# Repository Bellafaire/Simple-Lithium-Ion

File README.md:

# Simple Lithium Ion
A simple to use lithium ion boost, charge, and protection board designed to directly solder to standard 2.54mm perfboard for easier projects. For project logs and more in-depth information about the project please check out the project's hackaday.io page here: 
https://hackaday.io/project/167078-simple-lithium-ion

## Features
- On-board lithium ion charging 
- Over current protection
- Over/Under voltage protection
- 5V output from single battery cell

## License
MIT

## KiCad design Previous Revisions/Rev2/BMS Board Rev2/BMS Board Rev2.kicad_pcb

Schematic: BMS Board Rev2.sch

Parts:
C1, C2, C3, C4, C5: 10uF; C_0805_2012Metric
D1: LED; LED_0805_2012Metric
D2: SK34WA; D_SOD-123F
J1, J3: Conn_01x06_Male; PinHeader_1x06_P2.54mm_Vertical
J2: USB_B_Micro; USB_Micro-B_Molex_47346-0001
L1: 4.7u (BCIHP0730-4R7M); L_7x7x3
R1: 220; R_0805_2012Metric
R2: 1k; R_0805_2012Metric
R3: 2k; R_0805_2012Metric
R4: 100; R_0805_2012Metric
R5: 220k; R_0805_2012Metric
R6: 3.3k; R_0805_2012Metric
U1: DW01; SOT-23-6
U2: SLM4055; SOT-23-5
U3, U4: NCE3420; SOT-23
U5: MT3608; SOT-23-6

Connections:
BAT+: C3.1, C4.1, J1.1, J1.2, J1.3, L1.2, R4.2, U2.1, U5.4, U5.5
BAT-: C1.2, C2.2, C3.2, J1.4, J1.5, J1.6, J2.5 (GND), J2.6 (Shield), R3.2, U1.6, U2.2, U4.2
GND_Protected: C4.2, C5.2, J3.1, J3.2, J3.3, R2.2, R6.2, U3.3, U5.2
unnamed: C1.1, D1.2 (A), J2.1 (VBUS), U2.4
unnamed: C2.1, R4.1, U1.5
unnamed: C5.1, D2.1, J3.4, J3.5, J3.6, R5.1
unnamed: D1.1 (K), R1.1
unnamed: D2.2, L1.1, U5.1
unnamed: R2.1, U1.2
unnamed: R3.1, U2.5
unnamed: R5.2, R6.1, U5.3
unnamed: U1.1, U3.1
unnamed: U1.3, U4.1
unnamed: U3.2, U4.3
chrg_indicator: R1.2, U2.3

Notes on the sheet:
This resistor configuration yields a 4.6v output, please revise

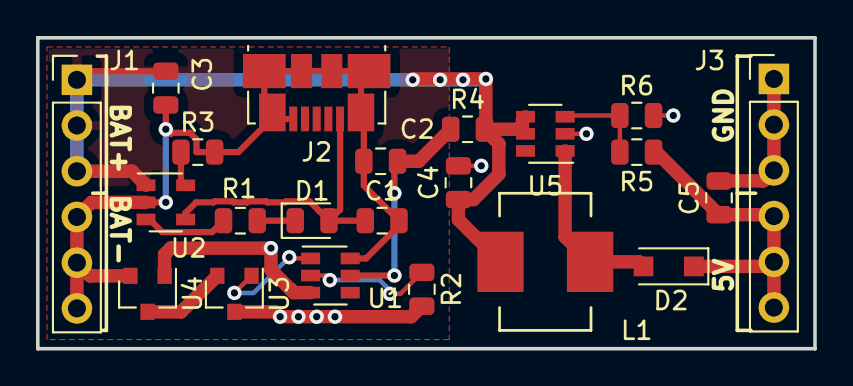
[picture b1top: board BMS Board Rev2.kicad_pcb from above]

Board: 2 copper layers, 43.2 x 17.3 mm, 22 parts (0 on the bottom side), 15 nets.

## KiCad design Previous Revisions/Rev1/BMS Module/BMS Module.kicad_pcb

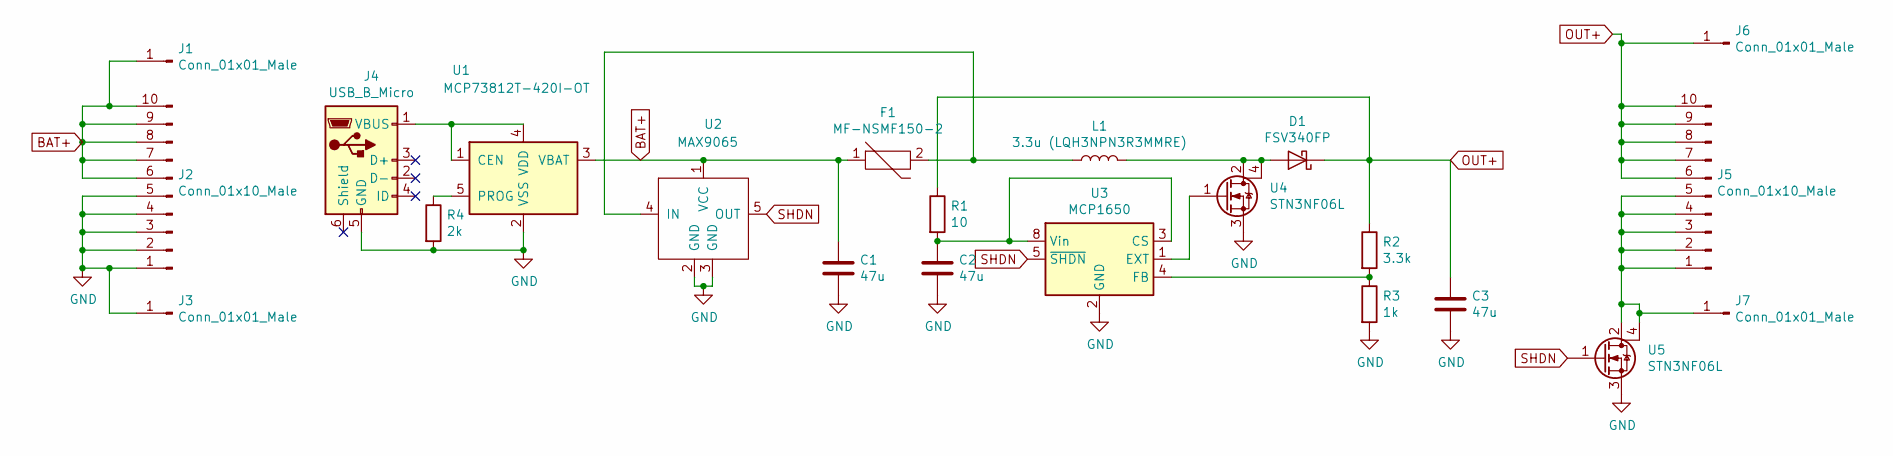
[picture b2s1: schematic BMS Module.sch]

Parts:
C1, C2, C3: 47u; C_1210_3225Metric
D1: FSV340FP; D_SOD-123
F1: MF-NSMF150-2; Fuse_1206_3216Metric
J1, J3, J6, J7: Conn_01x01_Male; PinHeader_1x01_P2.54mm_Vertical
J2, J5: Conn_01x10_Male; PinHeader_1x10_P2.54mm_Vertical
J4: USB_B_Micro; USB_Micro-B_GCT_USB3076-30-A
L1: 3.3u (LQH3NPN3R3MMRE); L_Taiyo-Yuden_MD-3030
R1: 10; R_0805_2012Metric
R2: 3.3k; R_0805_2012Metric
R3: 1k; R_0805_2012Metric
R4: 2k; R_0805_2012Metric
U1: MCP73812T-420I-OT; SOT-23-5
U2: MAX9065; SOT-23-5
U3: MCP1650; MSOP-8_3x3mm_P0.65mm
U4, U5: STN3NF06L; SOT-223

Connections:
BAT+: C1.1, F1.1, J1.1, J2.6, J2.7, J2.8, J2.9, J2.10, U1.3 (VBAT), U2.1 (VCC)
GND: C1.2, C2.2, C3.2, J2.1, J2.2, J2.3, J2.4, J2.5, J3.1, J4.5 (GND), R3.2, R4.2, U1.2 (VSS), U2.2 (GND), U2.3 (GND), U3.2 (GND), U4.3, U5.3
unnamed: C2.1, R1.2, U3.3 (CS), U3.8 (Vin)
unnamed: D1.2 (A), L1.2, U4.2, U4.4
unnamed: F1.2, L1.1, U2.4 (IN)
unnamed: J4.1 (VBUS), U1.1 (CEN), U1.4 (VDD)
unnamed: J5.1, J5.2, J5.3, J5.4, J5.5, J7.1, U5.2, U5.4
unnamed: R2.2, R3.1, U3.4 (FB)
unnamed: R4.1, U1.5 (PROG)
unnamed: U3.1 (EXT), U4.1
OUT+: C3.1, D1.1 (K), J5.6, J5.7, J5.8, J5.9, J5.10, J6.1, R1.1, R2.1
SHDN: U2.5 (OUT), U3.5 (~SHDN), U5.1

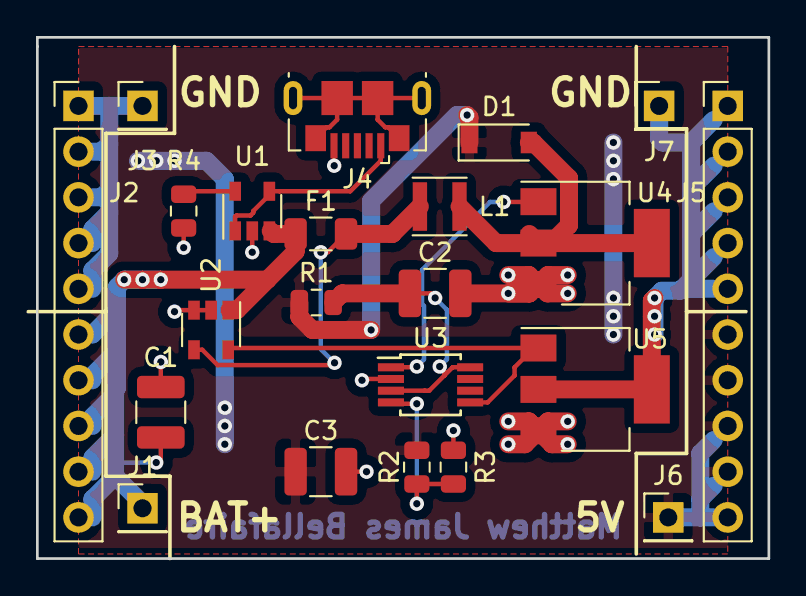
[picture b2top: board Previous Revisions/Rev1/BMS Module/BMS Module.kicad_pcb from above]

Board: 2 copper layers, 40.6 x 29.0 mm, 22 parts (0 on the bottom side), 12 nets.

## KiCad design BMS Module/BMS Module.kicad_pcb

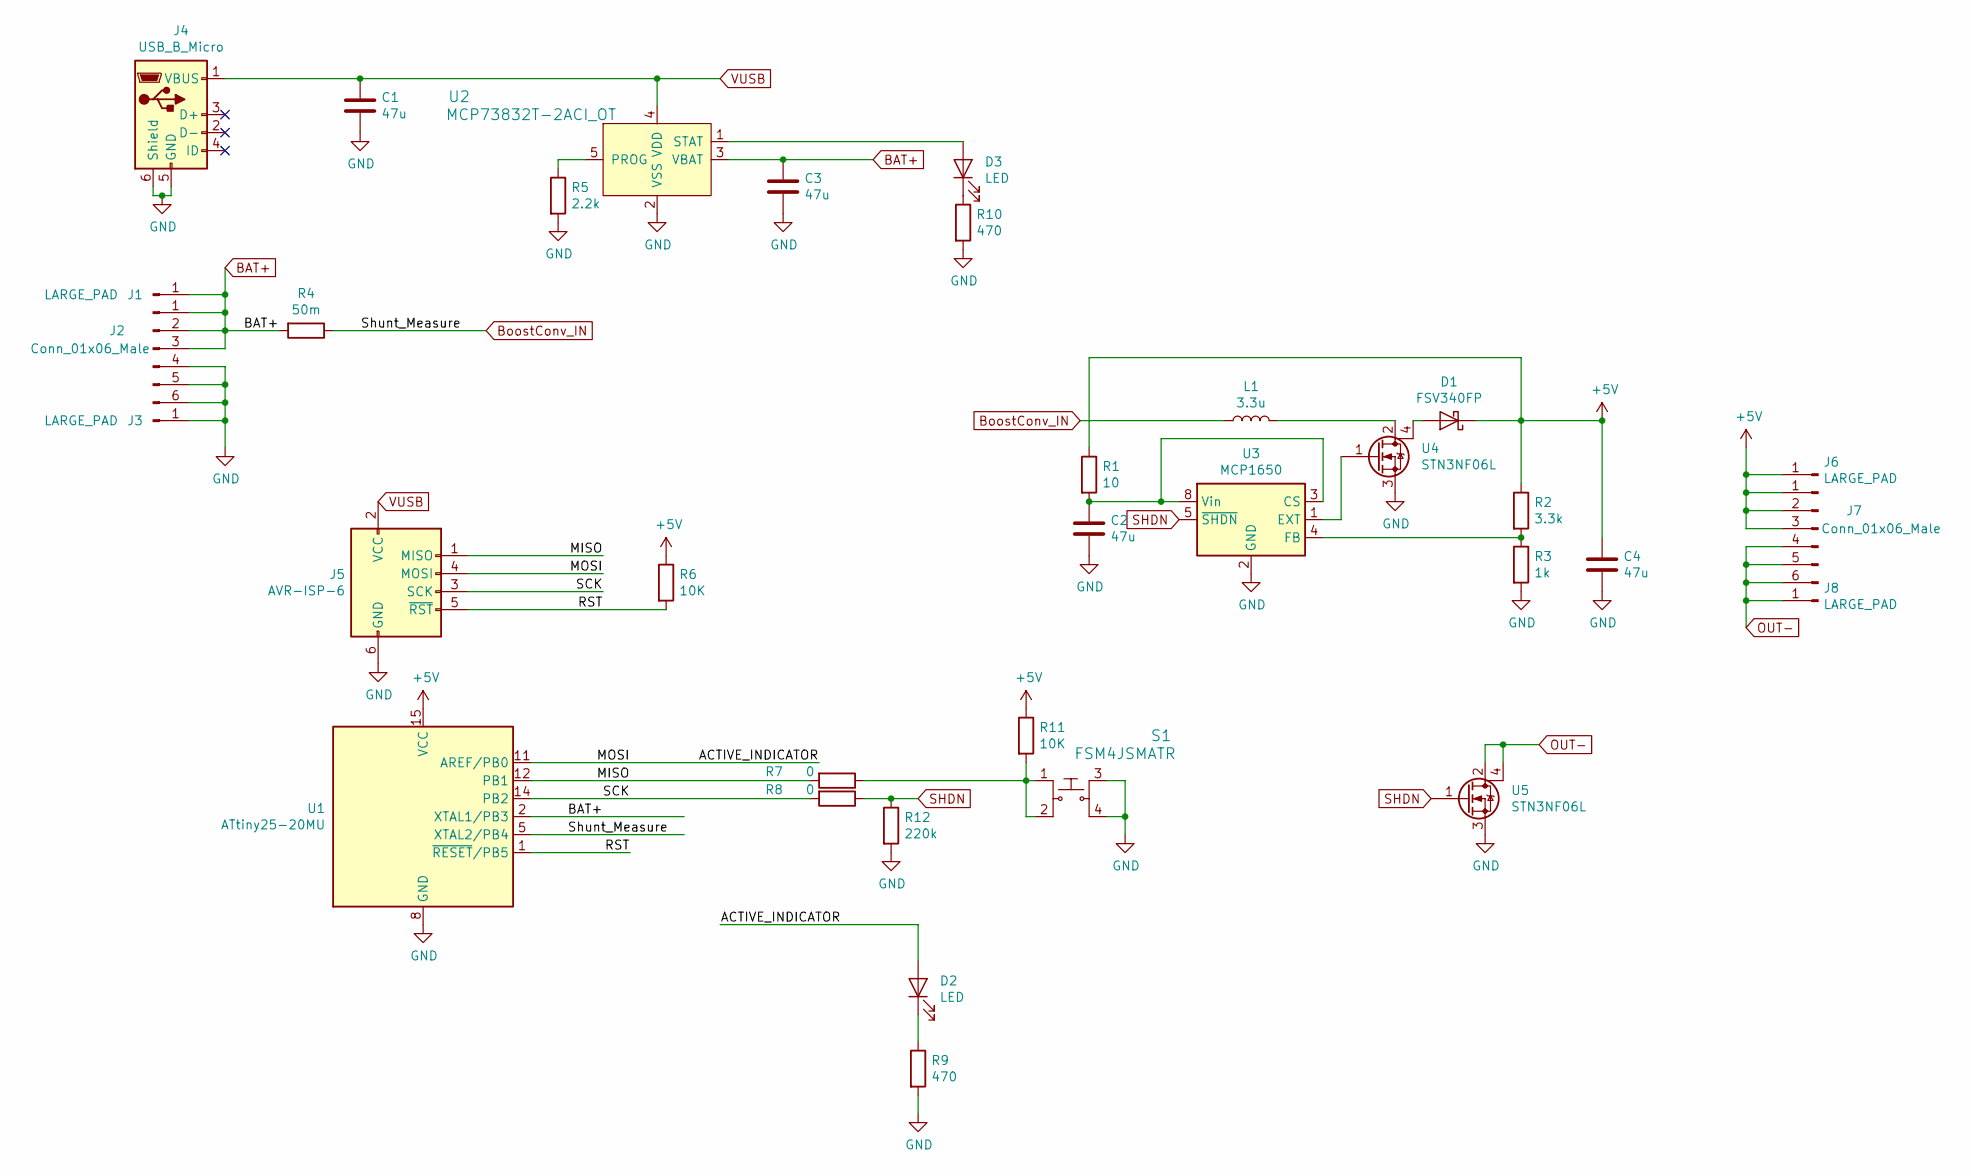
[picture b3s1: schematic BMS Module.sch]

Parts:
C1, C2, C3, C4: 47u; C_1210_3225Metric; digikey 1276-3064-1-ND
D1: FSV340FP; D_SOD-123; digikey FSV340FPCT-ND
D2, D3: LED; LED_0805_2012Metric_Castellated
J1, J3, J6, J8: LARGE_PAD
J2, J7: Conn_01x06_Male; PinHeader_1x06_P2.54mm_Vertical
J4: USB_B_Micro; USB_Micro_B_Female_10118192; digikey 609-4613-1-ND
J5: AVR-ISP-6; PinHeader_2x03_P2.54mm_Vertical
L1: 3.3u; ASPI-0630HI-3R3N-T15; digikey ASPI-0630HI-3R3M-T15CT-ND
R1: 10; R_0805_2012Metric
R2: 3.3k; R_0805_2012Metric
R3: 1k; R_0805_2012Metric
R4: 50m; R_2512_6332Metric; digikey YAG2156CT-ND
R5: 2.2k; R_0805_2012Metric
R6, R11: 10K; R_0805_2012Metric
R7, R8: 0; R_0805_2012Metric; digikey RMCF0805ZT0R00CT-ND
R9, R10: 470; R_0805_2012Metric; digikey A129745CT-ND
R12: 220k; R_0805_2012Metric
S1: FSM4JSMATR; Switch_Tactile_SMD_6x6mm; MPN FSM4JSMATR; digikey 450-1759-1-ND
U1: ATtiny25-20MU; QFN-20-1EP_4x4mm_P0.5mm_EP2.25x2.25mm; digikey 1611-ATTINY25V-15MTCT-ND
U2: MCP73832T-2ACI_OT; SOT-753; MPN MCP73832T-2ACI/OT; digikey MCP73832T-2ACI/OTCT-ND
U3: MCP1650; MSOP-8_3x3mm_P0.65mm; digikey MCP1650S-E/MS-ND
U4, U5: STN3NF06L; SOT-223; digikey 497-3177-1-ND

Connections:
+5V: C4.1, D1.1 (K), J6.1, J7.1, J7.2, J7.3, R1.1, R2.1, R6.1, R11.1, U1.15 (VCC)
/ACTIVE_INDICATOR: D2.2 (A), J5.4 (MOSI), U1.11 (AREF/PB0)
/MISO: J5.1 (MISO), R7.2, U1.12 (PB1)
/RST: J5.5 (~RST), R6.2, U1.1 (~RESET~/PB5)
/SCK: J5.3 (SCK), R8.2, U1.14 (PB2)
BAT+: C3.1, J1.1, J2.1, J2.2, J2.3, R4.2, U1.2 (XTAL1/PB3), U2.3 (VBAT)
BoostConv_IN: L1.1, R4.1, U1.5 (XTAL2/PB4)
GND: C1.2, C2.2, C3.2, C4.2, J2.4, J2.5, J2.6, J3.1, J4.5 (GND), J4.6 (Shield), J5.6 (GND), R3.2, R5.2, R9.2, R10.2, R12.2, S1.3, S1.4, U1.8 (GND), U1.21 (GND), U2.2 (VSS), U3.2 (GND), U4.3, U5.3
unnamed: C2.1, R1.2, U3.3 (CS), U3.8 (Vin)
unnamed: D1.2 (A), U4.4
unnamed: D2.1 (K), R9.1
unnamed: D3.1 (K), R10.1
unnamed: D3.2 (A), U2.1 (STAT)
unnamed: L1.2, U4.2
unnamed: R2.2, R3.1, U3.4 (FB)
unnamed: R5.1, U2.5 (PROG)
unnamed: R7.1, R11.2, S1.1, S1.2
unnamed: U3.1 (EXT), U4.1
OUT-: J7.4, J7.5, J7.6, J8.1, U5.2, U5.4
SHDN: R8.1, R12.1, U3.5 (~SHDN), U5.1
VUSB: C1.1, J4.1 (VBUS), J5.2 (VCC), U2.4 (VDD)

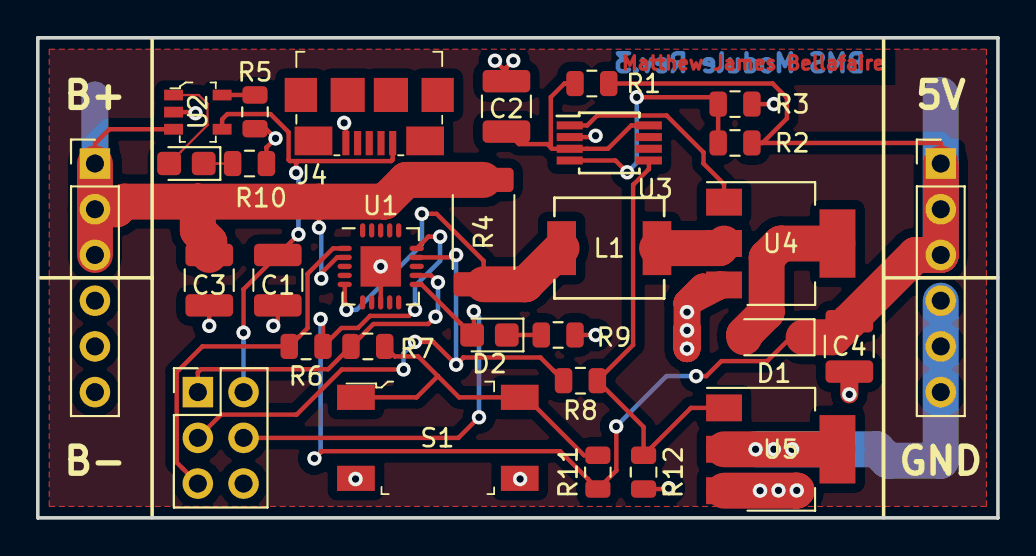
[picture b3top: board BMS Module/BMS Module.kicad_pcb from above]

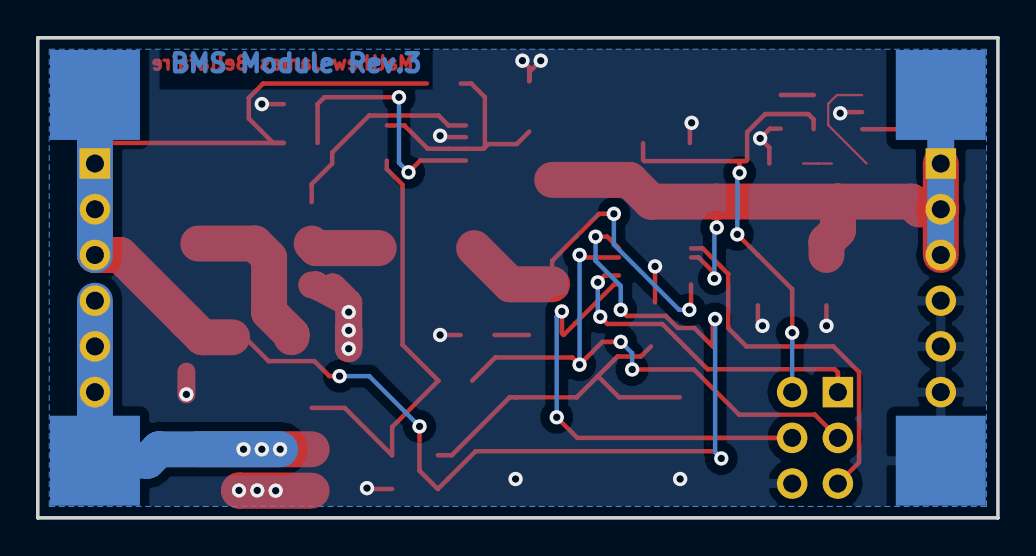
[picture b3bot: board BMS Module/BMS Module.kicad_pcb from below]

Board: 2 copper layers, 53.3 x 26.7 mm, 34 parts (4 on the bottom side), 21 nets.

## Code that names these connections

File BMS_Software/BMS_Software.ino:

#include <BatteryMonitor.h>
#define F_CPU 8000000
#include <util/delay.h> //using the arduino delay takes more flash than the util/delay.h hence why we use it instead. Actually saved about 100 bytes by doing this
#include <avr/sleep.h>
#include <avr/interrupt.h>

//be sure to enable Brown out detection at 2.7V
//core clock should be 1MHz to reduce power consumption.

#define ACTIVE_IND PB0
#define BUTTON PB1
#define SHDN PB2
#define BAT_POS 3          //ADC3
#define CURRENT_MEASURE 2  //ADC4

#define OVER_CURRENT_LIMIT 1.0
#define UNDER_VOLTAGE_THRESHOLD 3.0
#define ABSOLUTE_MINIMUM_VOLTAGE 2.7

#define BUTTON_HOLD_TO_SLEEP_MS 500
#define LOOP_DELAY 10

#define SLEEP_BUTTON_COUNT BUTTON_HOLD_TO_SLEEP_MS / LOOP_DELAY

int buttonHeldCounter = 0;

BatteryMonitor bat = BatteryMonitor(BAT_POS, CURRENT_MEASURE);

//disable sleep mode upon wakeup.
ISR (PCINT0_vect)
{
  //if the button is pressed then wakeup. pinchange on release doesn't count
    if (!(PINB & (1 << BUTTON))) {
      MCUCR &= ~(1 << SE);  //Disabling sleep mode inside interrupt routine
    }
}

void setup() {
  DDRB |= (1 << ACTIVE_IND) | (1 << SHDN);
  bat.setCurrentSenseResistance(0.05);

  //check if device has browned out.
  //if so there must have been an over current condition
  if (MCUSR & 0x04) {
    brownOutDetected();
  }

  //enable pinchange interrupt on button pin
  sei();
  GIMSK |= (1 << PCIE);
  PCMSK = (1 << PCINT1);
  set_sleep_mode(SLEEP_MODE_PWR_DOWN);

  //now that the check is complete we can activate the output ports
  PORTB = (1 << SHDN) | (1 << ACTIVE_IND);

}


void brownOutDetected() {
  PORTB &= ~((1 << SHDN) | (1 << ACTIVE_IND));
  while (1) {
    if (!(PINB & (1 << BUTTON))) {
      PORTB = (1 << SHDN) | (1 << ACTIVE_IND);
      MCUSR &= ~0x04; //clear brownout detection.
      return;
    }
    PORTB ^= (1 << ACTIVE_IND);
    _delay_ms(100);
  }
}


void overCurrentShutdown() {
  PORTB &= ~((1 << SHDN) | (1 << ACTIVE_IND));
  while (1) {
    for (int a = 0; a < 10; a++) {
      if (!(PINB & (1 << BUTTON))) {
        PORTB = (1 << SHDN) | (1 << ACTIVE_IND);
        return;
      }
      PORTB ^= (1 << ACTIVE_IND);
      _delay_ms(10);
    }
    _delay_ms(50);
  }
}

void lowVoltageShutdown() {
  PORTB &= ~(1 << SHDN);
  while (1) {
    if (!(PINB & (1 << BUTTON))) {
      PORTB = (1 << SHDN) | (1 << ACTIVE_IND);
      return;
    }
    PORTB ^= (1 << ACTIVE_IND);
    _delay_ms(25);
  }
}

void loop() {
  if (readBatMultiple(10) > UNDER_VOLTAGE_THRESHOLD) {
    if (readCurrentMultiple(10) < OVER_CURRENT_LIMIT) {
      PORTB = (1 << SHDN) | (1 << ACTIVE_IND);
    } else {
      overCurrentShutdown();
    }
  } else {
    lowVoltageShutdown();
  }

  if (!(PINB & (1 << BUTTON))) {
    rapidBlink();
    PORTB &= ~((1 << SHDN) | (1 << ACTIVE_IND));
    sleep_enable();
    set_sleep_mode(SLEEP_MODE_PWR_DOWN);
    sleep_cpu();
  }
}


void rapidBlink() {
  for (int a = 0; a < 6; a++) {
    PORTB ^= (1 << ACTIVE_IND);
    _delay_ms(10);
  }
}


float readCurrentMultiple(int reads) {
  float total = 0;
  for (int a = 0; a < reads; a++) {
    total += bat.getBatteryCurrent();
  }
  return total / reads;
}

float readBatMultiple(int reads) {
  float total = 0;
  for (int a = 0; a < reads; a++) {
    total += bat.getCurrentBatteryVoltage();
  }
  return total / reads;
}

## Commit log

2021-05-08 Commit of all revision 3 files from project
2021-05-08 Commit of files from previous revisions
2021-05-09 added brown out detection, device can now also be put into sleep mode by holding button.
2021-05-09 corrected pin declarations
2021-05-09 update to readme
